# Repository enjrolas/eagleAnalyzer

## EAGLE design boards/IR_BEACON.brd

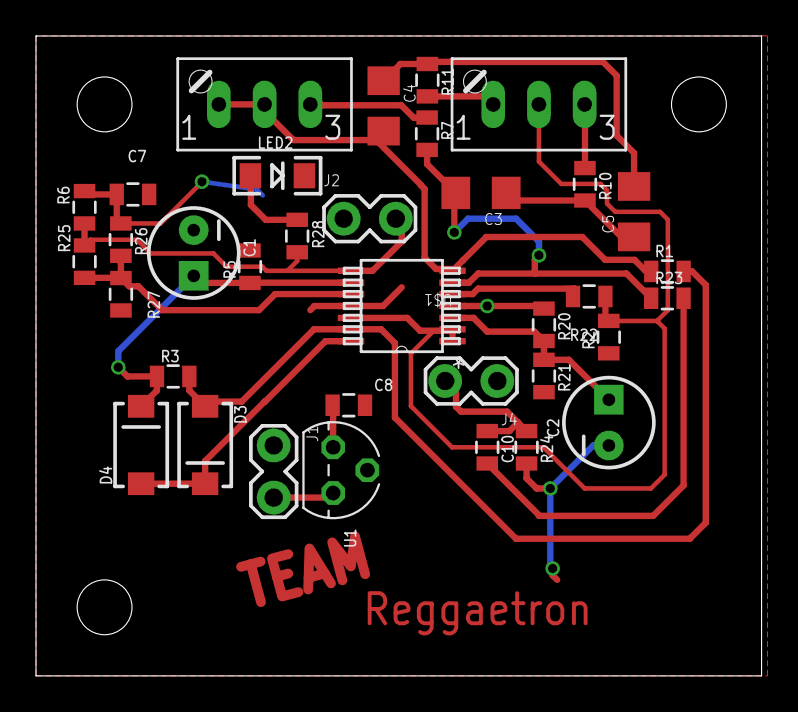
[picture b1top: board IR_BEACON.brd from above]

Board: 2 copper layers, 40.3 x 35.5 mm, 38 parts (0 on the bottom side), 21 nets.

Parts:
1K, 10K: S64W
C1, C2: CPOL-RADIAL-10UF-25V
C3, C4, C5: 47nF; 1206
C7: .1uF; 0805
C8: 2.2uF; 0805
C10: 100nF; 0805
D3, D4: DIODE-SCHOTTKY_; SMA-DIODE
J1, J2, J4: 1X02_LOCK
JP1, JP3, JP5: STAND-OFFTIGHT; STAND-OFF-TIGHT
LED2: LED-1206
R1, R2, R3, R5, R7, R20, R21: 10k; 0805
R6: 3.9k; 0805
R10: 100; 0805
R11, R24: 2.2k; 0805
R22: 20k; 0805
R23: 4.7k; 0805
R25: 1M; 0805
R26: 100k; 0805
R27: 144k; 0805
R28: 330; 0805
U1: LP2950-3.0ACZ; TO92
U$1: MCP6024-X/ST; TSSOP14_MC

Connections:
GND: C1.2, C2.2, C7.2, C8.2, J1.1, J2.1, LED2.C, R5.2, R21.2, R24.2, R27.2, U1.2, U$1.11
unnamed: D3.A, R1.2, R3.2, U$1.13
unnamed: C3.2, R7.2, R23.1, U$1.6
unnamed: 1K.A, R11.2
unnamed: 10K.E, R7.1
unnamed: C3.1, C5.1, R10.2
unnamed: C4.1, C5.2, R11.1
unnamed: 1K.E, R10.1
unnamed: D3.C, D4.A, U$1.14
unnamed: C2.1, R20.2, R21.1, U$1.3
unnamed: R22.2, U$1.5
unnamed: C10.2, R23.2
unnamed: LED2.A, R28.2
VCC: C7.1, C8.1, J4.1, R6.1, R20.1, R26.1, U1.1, U$1.4
VINC+: R25.1, R26.2, R27.1, U$1.10
VOUTC: J2.2, R6.2, R25.2, R28.1, U$1.8
V_BIAS: 1K.S, R2.2, R22.1, U$1.1, U$1.2, U$1.12
V_ENV1: C1.1, D4.C, R3.1, R5.1, U$1.9
V_FILT: 10K.A, 10K.S, C4.2, R1.1, U$1.7
V_IN: J1.2, U1.3
V_IR: C10.1, J4.2, R24.1

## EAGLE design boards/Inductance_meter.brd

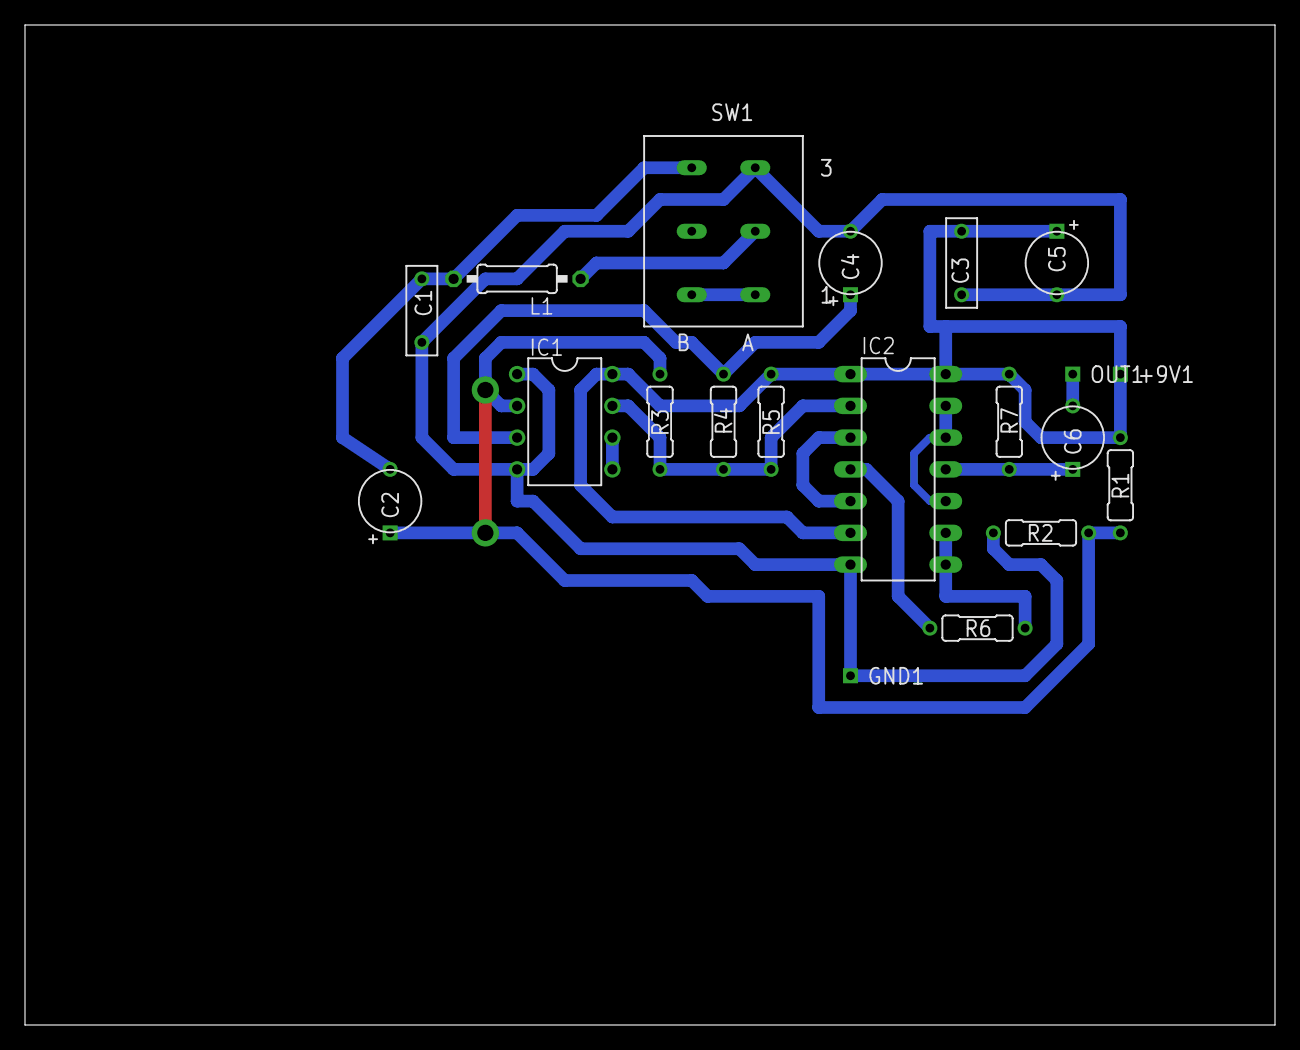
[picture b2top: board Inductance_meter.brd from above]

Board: 2 copper layers, 100.0 x 80.0 mm, 20 parts (0 on the bottom side), 15 nets.

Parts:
+9V1: +9V(T); SQUARE
C1: 970pF; 072X025
C2, C4: 10uF; 050_020_2
C3: 0,1uF; 072X025
C5, C6: 100uF; 050_020_2
GND1: GND(T); SQUARE
IC1: LM311N; DIL08
IC2: 4011N; DIL14
L1: 68uH; 0207/10
OUT1: OUT(T); SQUARE
R1, R2, R3: 100K; R0207/3
R4: 47K; R0207/3
R5, R7: 1K; R0207/3
R6: 150R; R0207/3
SW1: DPDT

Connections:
+9V: +9V1.1, C3.2, C5.+, IC1.8, IC2.1, IC2.6, IC2.14, R1.2, R5.2, R7.1
GND: C1.2, C3.1, C4.-, C5.-, GND1.1, IC1.1, IC1.4, IC2.7, R2.1, SW1.A3
unnamed: L1.1, SW1.A2
unnamed: C1.1, C2.-, L1.2, SW1.B3
unnamed: SW1.A1, SW1.B1
unnamed: IC1.7, IC2.2, R3.1, R4.2, R5.1
unnamed: C2.+, IC1.2, R1.1, R2.2, R3.2
unnamed: IC2.4, R6.2
unnamed: IC1.5, IC1.6
unnamed: C4.+, IC1.3, R4.1
unnamed: IC2.3, IC2.5
unnamed: IC2.8, IC2.9, R6.1
unnamed: IC2.10, IC2.12, IC2.13
unnamed: C6.+, IC2.11, R7.2
OUT: C6.-, OUT1.1

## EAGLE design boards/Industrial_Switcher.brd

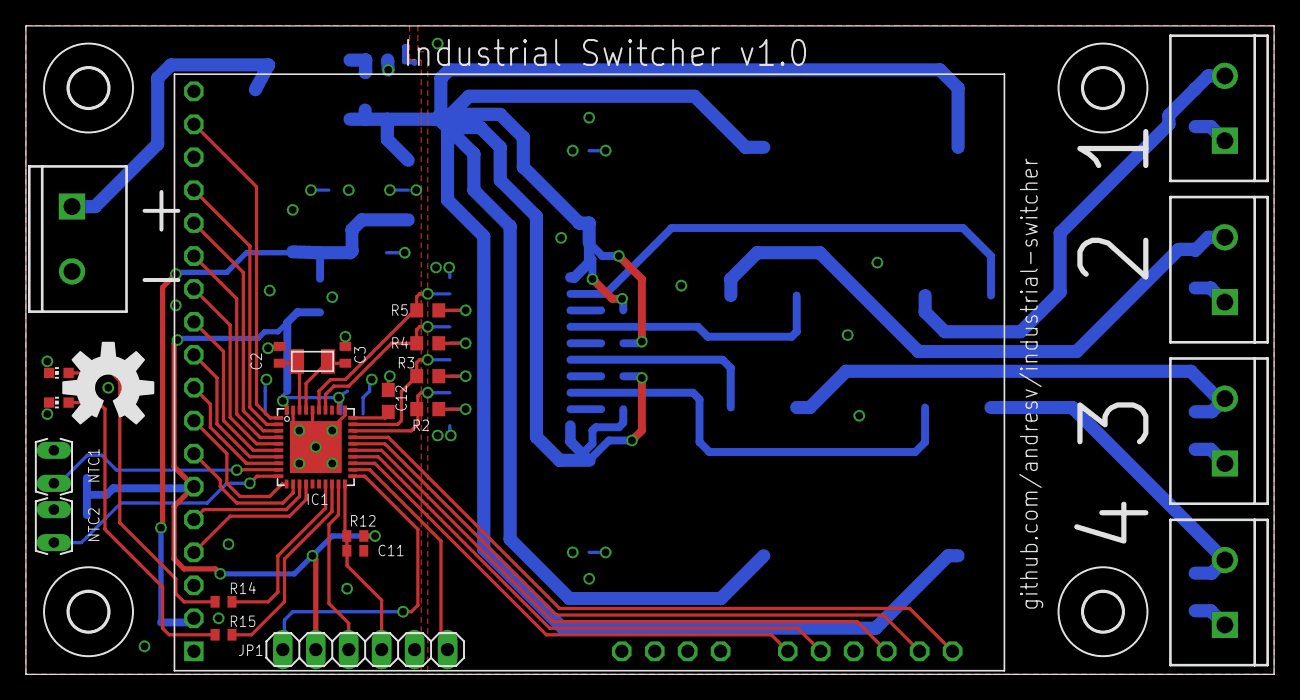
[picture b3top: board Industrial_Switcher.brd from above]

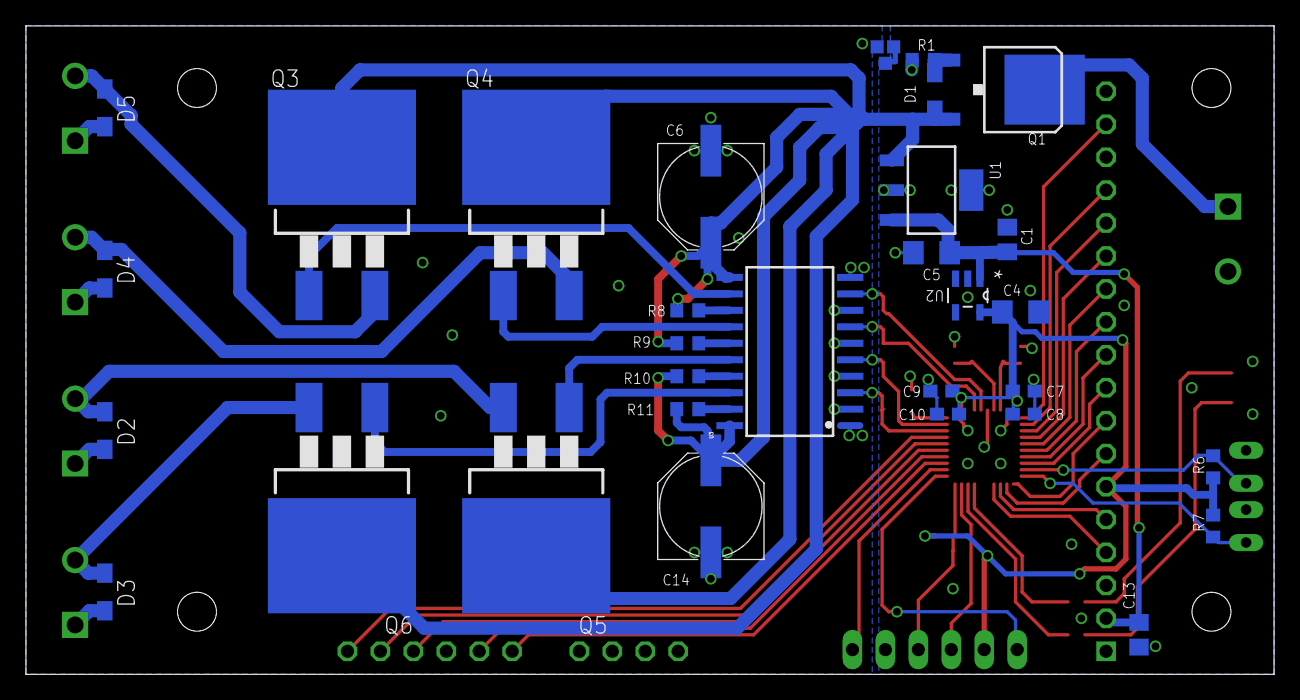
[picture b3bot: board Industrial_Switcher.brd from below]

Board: 2 copper layers, 96.2 x 50.0 mm, 60 parts (31 on the bottom side), 57 nets.

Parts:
C1: 4.7uF; C0805
C2, C3: 9 pF; C0402
C4: 4.7uF; C1206
C5: 10 uF; C1206
C6, C14: 68uF; PANASONIC_F
C7, C9: 10uF; C0603
C8, C10: 100nF; C0603
C11: 2.2nF; C0402
C12: 470nF; C0603
C13: 1uF; C0805
D1: 10V; SOD323-W
D2, D3, D4, D5: 1N4148WS; SOD323-W
H1, H2, H3, H4: 3,0
IC1: MSP430FR5739; RHA40
IC2: HY-TFT220; 2.2TFT
JP1: 1X06
LED1, LED2: CHIP-LED0603
LOAD1, LOAD2, LOAD3, LOAD4: SCREWTERMINAL-5MM-2
LOGO2: OSHW-LOGOL; OSHW-LOGO-L
NTC1, NTC2: 4k7; N640
POWER: SCREWTERMINAL-5MM-2
Q1: IRFR5305; D-PAK_TO252AA
Q2: 32 kHz; ABS07
Q3, Q4, Q5, Q6: IRFZ34NS; D2PACK
R1: 100k; R0603
R2, R3, R4, R5: 2k; R0603
R6, R7: 1k; R0603
R8, R9, R10, R11: 0.01; R0603
R12: 47k; R0402
R14, R15: 1k; R0402
U1: TDA3664; DRFRIEDPARTS/DOAAZ
U2: TPS76933; SOT95P280X145-5N
U3: LT1161CSWPBF; ANDRESV/B3JU7
U$1: GND_CONNECT

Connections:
+3V3: C4.1, C7.2, C8.2, C9.1, C10.1, IC1.32, IC1.40, IC2.RD, JP1.2, R6.2, R7.2, R12.2, U2.5
+5V: C1.1, C5.1, C13.2, IC2.5V, U1.3, U2.1
+24V: C6.+, C14.+, D1.C, Q1.3, Q3.2, Q4.2, Q5.2, Q6.2, R8.2, R9.2, R10.2, R11.2, U1.1, U3.11, U3.20
CS: IC1.2, IC2.CS
DB0: IC1.12, IC2.DB0
DB1: IC1.11, IC2.DB1
DB2: IC1.8, IC2.DB2
DB3: IC1.7, IC2.DB3
DB4: IC1.6, IC2.DB4
DB5: IC1.5, IC2.DB5
DB6: IC1.4, IC2.DB6
DB7: IC1.3, IC2.DB7
DCLK: IC1.27, IC2.DCLK
DCS: IC1.26, IC2.CS1
DIN: IC1.25, IC2.DIN
DIRQ: IC1.23, IC2.PIRQ
DOUT: IC1.24, IC2.DOUT
GND: C1.2, C2.2, C3.2, C4.2, C5.2, C7.1, C8.1, C9.2, C10.2, C11.2, C12.2, C13.1, IC1.31, IC1.36, IC1.39, IC1.TP, IC2.GND, JP1.5, LED1.C, LED2.C, NTC1.1, NTC2.1, POWER.2, R1.1, U1.2, U1.4, U2.2, U2.3, U$1.1, U$1.3
GNDA: C6.-, C14.-, D2.A, D3.A, D4.A, D5.A, LOAD1.1, LOAD2.1, LOAD3.1, LOAD4.1, U3.1, U3.10, U$1.2
LCDRESET: IC1.1, IC2.RESET
LED1: IC1.17, R14.2
LED2: IC1.18, R15.2
unnamed: D1.A, Q1.1, R1.2
unnamed: R5.2, U3.8
unnamed: R8.1, U3.13
unnamed: R9.1, U3.15
unnamed: D3.C, LOAD4.2, Q6.3
unnamed: R10.1, U3.17
unnamed: R4.2, U3.6
unnamed: D2.C, LOAD3.2, Q5.3
unnamed: R11.1, U3.19
unnamed: R3.2, U3.4
unnamed: D4.C, LOAD2.2, Q4.3
unnamed: POWER.1, Q1.4
unnamed: R2.2, U3.2
unnamed: D5.C, LOAD1.2, Q3.3
unnamed: Q6.1, U3.18
unnamed: C3.1, IC1.37, Q2.1
unnamed: C2.1, IC1.38, Q2.2
unnamed: C12.1, IC1.30
unnamed: Q5.1, U3.16
unnamed: Q4.1, U3.14
unnamed: Q3.1, U3.12
unnamed: LED1.A, R14.1
unnamed: LED2.A, R15.1
NTC1: IC1.9, NTC1.2, R6.1
NTC2: IC1.10, NTC2.2, R7.1
OUT1: IC1.28, R2.1, U3.3
OUT2: IC1.29, R3.1, U3.5
OUT3: IC1.34, R4.1, U3.7
OUT4: IC1.35, R5.1, U3.9
RS: IC1.14, IC2.RS
RX: IC1.22, JP1.6
SBWTCK: IC1.19, JP1.3
SBWTDIO: C11.1, IC1.20, JP1.4, R12.1
TX: IC1.21, JP1.1
WR: IC1.13, IC2.WR

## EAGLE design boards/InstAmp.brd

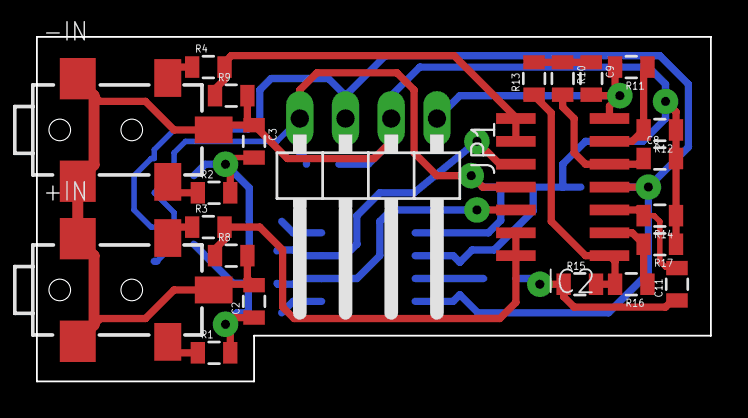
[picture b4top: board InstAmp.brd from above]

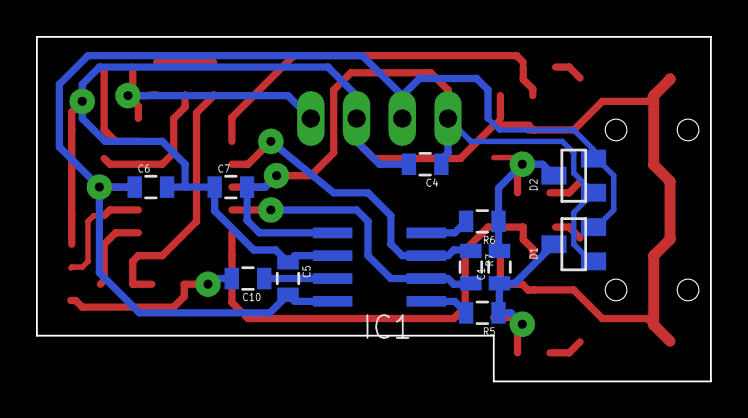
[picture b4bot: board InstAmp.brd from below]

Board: 2 copper layers, 37.4 x 19.1 mm, 35 parts (12 on the bottom side), 24 nets.

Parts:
+IN: AUDIOJACK2.5-SMD
-IN: AUDIOJACK2.5-SMD
C1: 10pF; 0805
C2, C3: 100pF; 0805
C4, C5, C6, C7: 100nF; 0805
C8: 47nF; 0805
C9: 33nF; 0805
C10, C11: 1uF; 0805
D1, D2: BAV199; SOT23
IC1: AD8221ARZ
IC2: TLC2254ID; SO14
JP1: OUT; 1X04/90
R1, R2, R5, R6: 2k2; 0805
R3, R4: 100; 0805
R7: 2k; 0805
R8, R9, R10, R11, R12, R13, R14, R17: 100k; 0805
R15: 680k; 0805
R16: 910k; 0805

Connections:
+5V: C5.2, C6.1, D1.2, D2.2, IC1.8, IC2.4, JP1.3
-5V: C4.1, C7.2, D1.1, D2.1, IC1.5, IC2.11, JP1.4
GND: +IN.GND1, +IN.GND2, +IN.SW, -IN.GND1, -IN.GND2, -IN.SW, C2.2, C3.1, C4.2, C5.1, C6.2, C7.1, C8.2, IC1.6, JP1.2, R8.2, R9.2, R12.1, R14.1, R17.1
unnamed: +IN.L, R1.1
unnamed: -IN.R, R4.1
unnamed: +IN.R, R3.1
unnamed: -IN.L, R2.1
unnamed: C1.2, C3.2, D2.3, R2.2, R6.1
unnamed: C1.1, C2.1, D1.3, R1.2, R5.1
unnamed: IC2.8, IC2.9, R4.2, R9.1
unnamed: IC1.3, IC2.10, R7.1
unnamed: IC2.1, R13.1, R15.2, R16.2
unnamed: IC2.2, R16.1, R17.2
unnamed: C10.1, IC1.7
unnamed: IC1.1, R5.2
unnamed: IC1.4, R6.2
unnamed: C8.1, IC2.5, R10.2
unnamed: C9.1, R10.1, R13.2
unnamed: IC1.2, IC2.12, R7.2
unnamed: IC2.13, IC2.14, R3.2, R8.1
unnamed: C10.2, C11.1, R15.1
unnamed: C11.2, IC2.3, R14.2
unnamed: IC2.6, R11.1, R12.2
OUT: C9.2, IC2.7, JP1.1, R11.2

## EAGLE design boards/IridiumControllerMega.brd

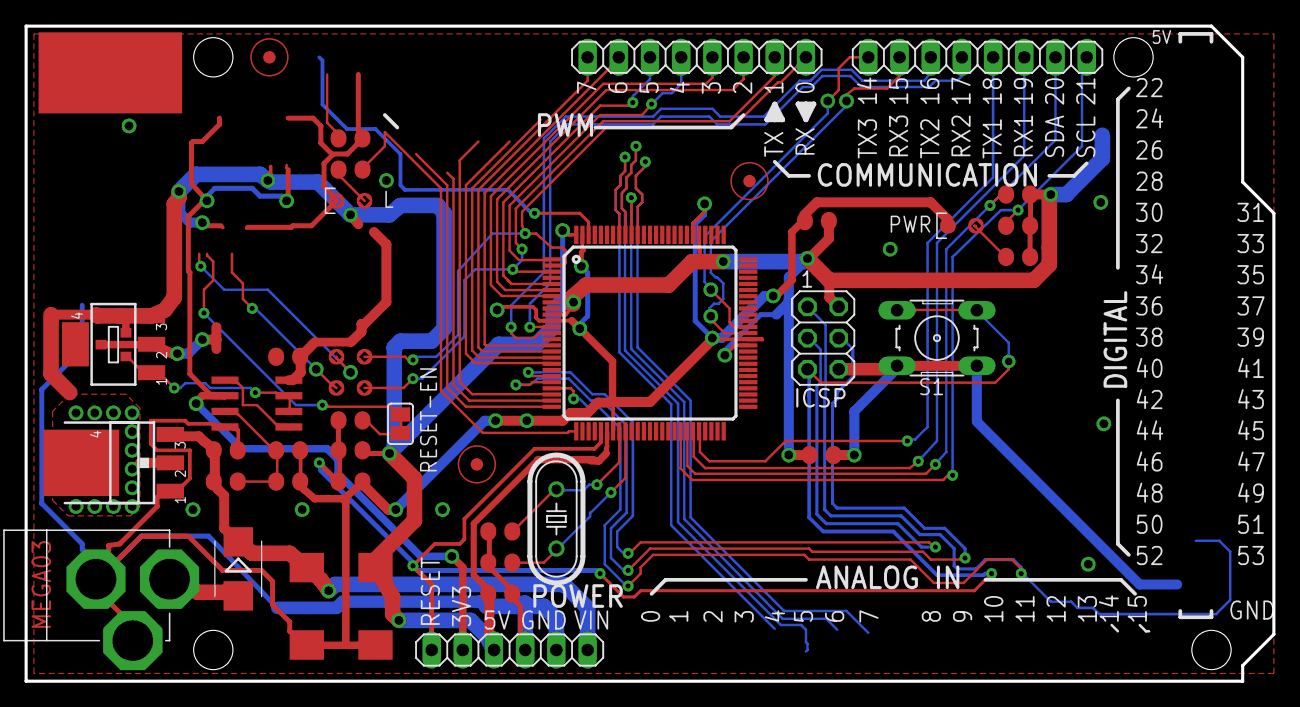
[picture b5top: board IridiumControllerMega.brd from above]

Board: 2 copper layers, 101.6 x 53.3 mm, 42 parts (0 on the bottom side), 35 nets.

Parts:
C1, C4, C5, C9, C10, C12, C13, C17: 100n; C0805RND
C2, C3, C11: 22p; C0805RND
C6, C7: 100u; SMC_D
COMMUNICATION: 1X08
D1: SMB
IC2: ATMEGA1280-16AU; TQFP100
IC4: MC33269D-5.0; DPACK
IC5: MC33269ST-5.0T3; SOT223
IC7: LM358D; SO08
ICSP: ICSP; 2X03
L: 0805RND
POWER: 1X06
PWML: 1X08
PWR: 0805RND
Q2: 16MHz; HC49/S
R1, R8: 1K; R0805RND
R2, R3, R6, R10: 10k; R0805RND
R5: 10K; R0805RND
R11, R12: 1K; RCL_0805RND
RESET-EN: SJ
S1: B3F-10XX
T1: NDT2955; SOT223
T2: FDN340P; SOT-23
U$1, U$2, U$3: FIDUCIALMOUNT; FIDUCIA-MOUNT
X2: DC21MMX; DC-21MM

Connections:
+3V3: IC7.2, POWER.2
+5V: C1.1, C7.+, C9.1, C10.1, C17.2, IC2.10, IC2.31, IC2.61, IC2.80, IC2.100, IC4.2, IC5.2, IC5.4, IC7.8, ICSP.2, POWER.3, R2.1, R3.1, R5.2, R8.1, T1.3, T2.2
AREF: C4.1, IC2.98
CMP: C13.2, IC7.3, R6.2, R10.1
DTR: C12.1, RESET-EN.1, RESET-EN.2
GATE_CMD: IC7.6, IC7.7, T1.1, T2.3
GND: C1.2, C2.1, C3.1, C4.2, C5.2, C6.-, C7.-, C9.2, C10.2, C11.2, C13.1, C17.1, IC2.11, IC2.32, IC2.62, IC2.81, IC2.99, IC4.1, IC5.1, IC7.4, ICSP.6, L.P$2, POWER.4, POWER.5, PWR.P$2, R6.1, S1.1, S1.2, X2.1, X2.3
unnamed: L.P$1, R1.2
unnamed: PWR.P$1, R8.2
unnamed: IC7.1, IC7.5
unnamed: C2.2, IC2.34, Q2.1
unnamed: C3.2, IC2.33, Q2.2
PB1: IC2.20, ICSP.3
PB2: IC2.21, ICSP.4
PB3: IC2.22, ICSP.1
PB7: IC2.26, R1.1
PE0: IC2.2, PWML.1, R11.P$2
PE1: IC2.3, PWML.2, R12.P$2
PE4: IC2.6, PWML.3
PE5: IC2.7, PWML.4
PG5: IC2.1, PWML.5
PH3: IC2.15, PWML.7
PH4: IC2.16, PWML.8
PWRIN: D1.A, X2.2
RESET: C11.1, C12.2, IC2.30, ICSP.5, POWER.1, R5.1, S1.3, S1.4
RXD1: COMMUNICATION.3, IC2.45
RXD2: COMMUNICATION.5, IC2.12
RXD3: COMMUNICATION.7, IC2.63
SCL: COMMUNICATION.1, IC2.43, R2.2
SDA: COMMUNICATION.2, IC2.44, R3.2
TXD1: COMMUNICATION.4, IC2.46
TXD2: COMMUNICATION.6, IC2.13
TXD3: COMMUNICATION.8, IC2.64
USBVCC: T1.2, T2.1
VIN: C5.1, C6.+, D1.C, IC4.3, IC5.3, POWER.6, R10.2

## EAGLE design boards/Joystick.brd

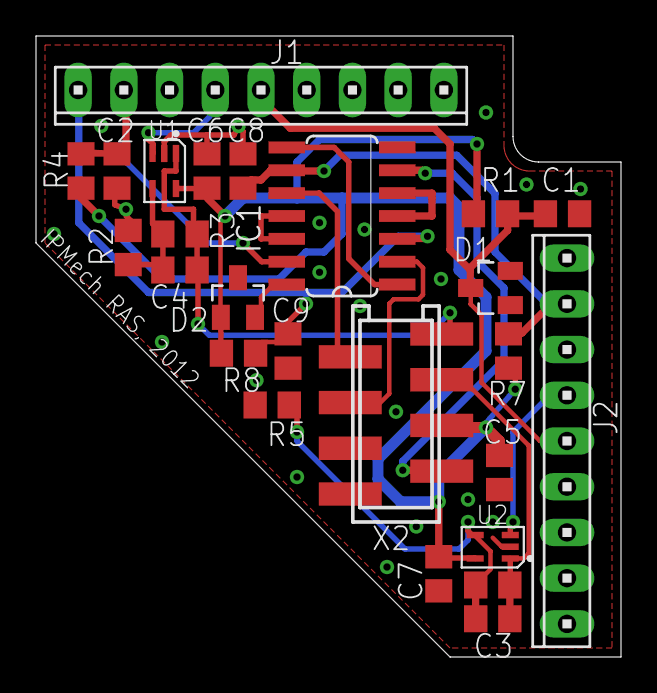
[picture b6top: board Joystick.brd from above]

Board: 2 copper layers, 32.5 x 34.5 mm, 25 parts (0 on the bottom side), 19 nets.

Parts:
C1, C2, C8, C9: 1uF; C0805
C3, C4, C6, C7: 0.1uF; C0805
C5: 10uF; C0805
D1: BZX84-C4V7; SOT23
D2: BAV199; SOT23
IC1: 74HC14D; SO14
J1, J2: 10X09MTA
R1: 100R 5%; R0805
R2, R5: 2K5 1%; R0805
R3, R6: 1K6 1%; R0805
R4, R7, R8: 1K 5%; R0805
U1, U2: AD8627AKS; SC70(KS-5)
X2: 7-188275-8; MMT-F-SMD-8

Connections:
+4V7: C1.1, D1.3, J1.5, J2.5, R1.2
+5V: C5.1, C6.1, C7.1, D2.1, R1.1, R4.2, R7.2, R8.2, U1.5, U2.5, X2.5
GNDA: C1.2, C2.2, C5.2, C6.2, C7.2, C8.2, C9.2, D1.1, IC1.7, J1.3, J1.7, J1.8, J1.9, J2.1, J2.3, J2.7, J2.8, J2.9, R2.1, R5.1, U1.2, U2.2, X2.6
unnamed: J2.4, U2.3
unnamed: C3.1, R5.2, R6.1, U2.4
unnamed: C3.2, R6.2, U2.1, X2.3
unnamed: IC1.4, IC1.5
unnamed: IC1.10, X2.2
unnamed: D2.2, IC1.14
unnamed: IC1.11, IC1.12
unnamed: IC1.1, IC1.8
unnamed: C2.1, IC1.13, J1.2, R4.1
unnamed: IC1.2, X2.4
unnamed: C8.1, IC1.9, J2.2, R7.1
unnamed: C9.1, IC1.3, J1.1, R8.1
unnamed: J1.4, U1.3
unnamed: C4.1, R2.2, R3.1, U1.4
unnamed: C4.2, R3.2, U1.1, X2.1
TOTMANN_TASTE: IC1.6, X2.7

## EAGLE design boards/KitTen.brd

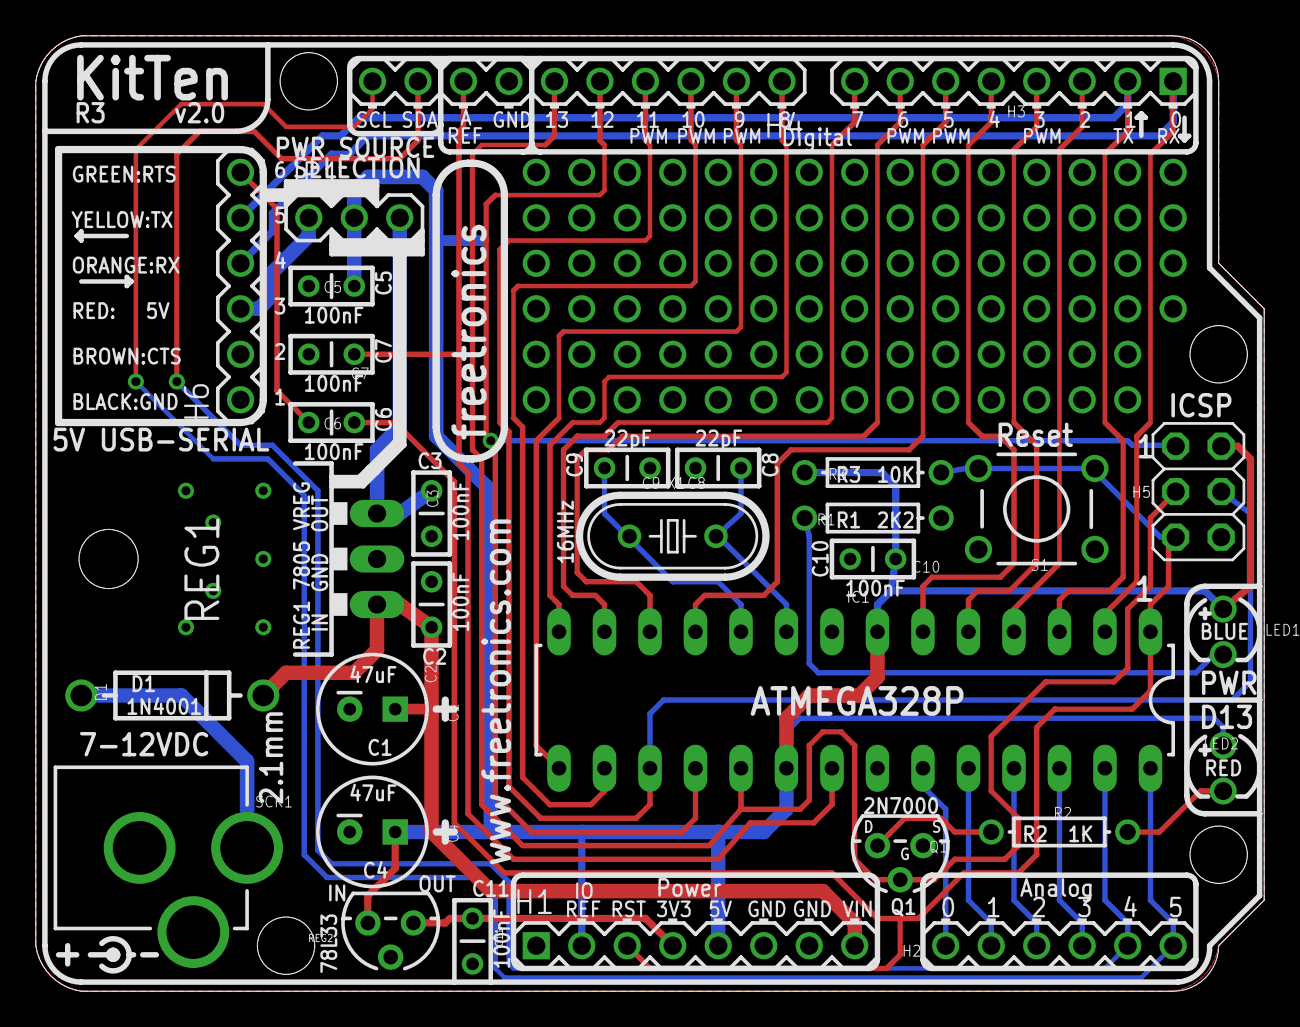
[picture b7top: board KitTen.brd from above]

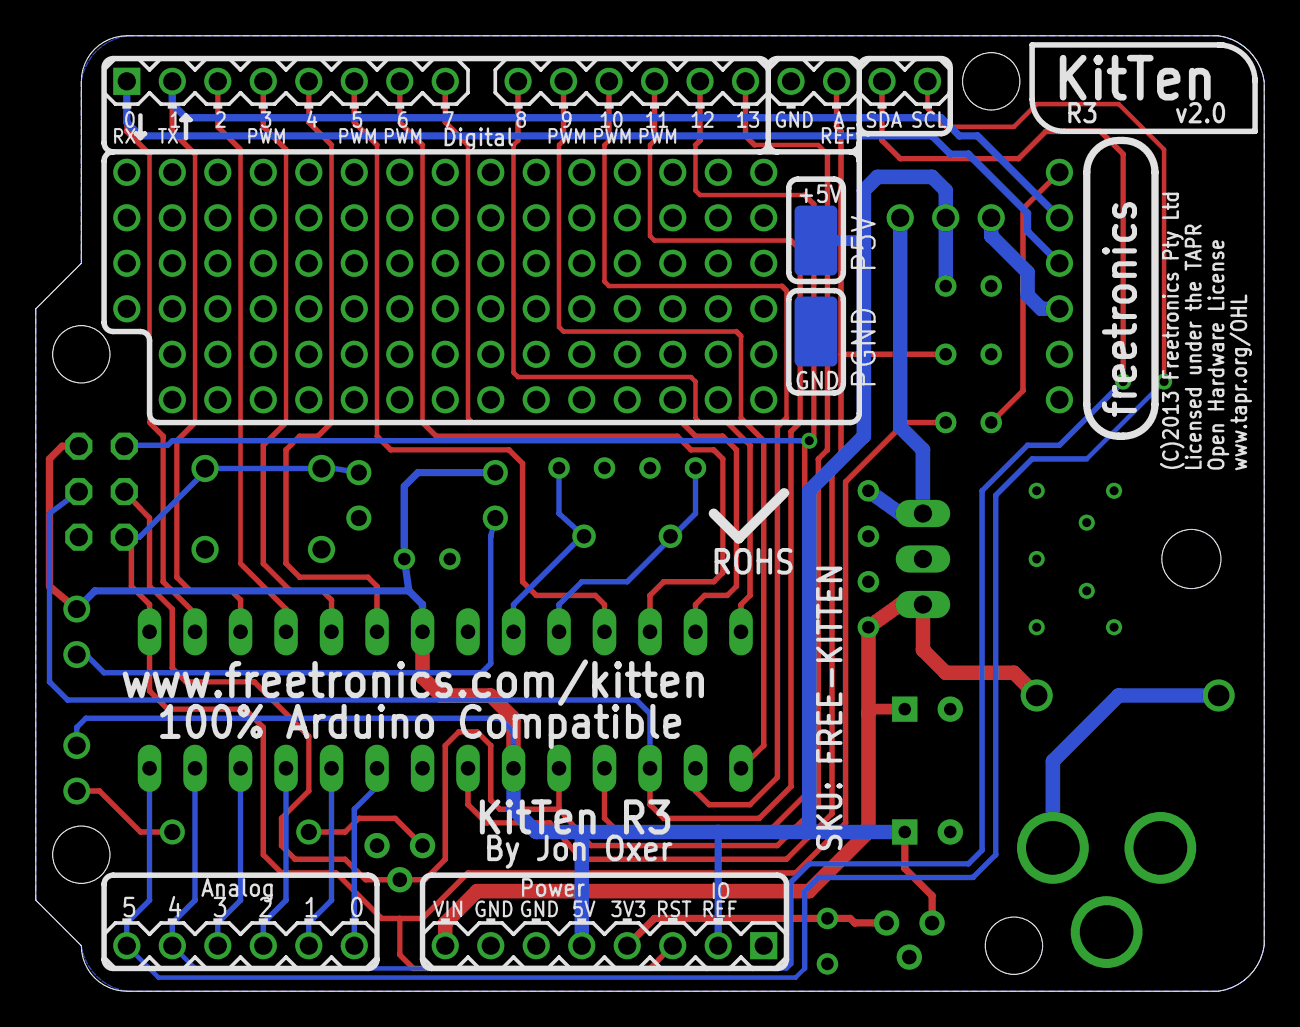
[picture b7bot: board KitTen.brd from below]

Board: 2 copper layers, 68.6 x 53.3 mm, 33 parts (2 on the bottom side), 35 nets.

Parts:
C1, C4: 47uF 25V; CPOL-RADIAL-10UF-25V
C2, C3, C5, C6, C7, C10, C11: 100nF; CAP-PTH-SMALL
C8, C9: 22pF; CAP-PTH-SMALL
D1: 1N4001; DIODE-1N4001
H1, H3: Digital_0_7; 1X08
H2: Analog; 1X06
H4: M100.1; 1X10
H5: ICSP; 2X03
H6: USB-TTL; 1X06
IC1: ATMEGA328P; DIL28-3
JP1: PWR SELECT; 1X03
LED1: PWR/BLUE; LED3MM
LED2: D13; LED3MM
P5V: LUXEON-PAD
PGND: LUXEON-PAD
Q1: 2N7000; TO92
R1: 2K2; AXIAL-0.3
R2: 1K; AXIAL-0.3
R3: 10K; AXIAL-0.3
REG1: 7805; 78XXL
REG2: 78L33; TO92
S1: RESET; TACTILE-PTH
SCK1: DC_2_1MM; POWER_JACK_PTH
X1: 16MHz HC49S; HC49U-V

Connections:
3V3: C11.1, H1.4, REG2.1
5V: C4.1, C5.1, C10.1, H1.2, H1.5, H5.2, IC1.7, IC1.20, JP1.2, LED1.A, LED2.A, P5V.P$1, R3.P$2, REG2.3
A0: H2.1, IC1.23
A1: H2.2, IC1.24
A2: H2.3, IC1.25
A3: H2.4, IC1.26
A4_SDA: H2.5, H4.9, IC1.27
A5_SCL: H2.6, H4.10, IC1.28
AREF: C7.1, H4.8, IC1.21
D0_RX: H3.1, H6.4, IC1.2
D1_TX: H3.2, H6.5, IC1.3
D2: H3.3, IC1.4
D3: H3.4, IC1.5
D4: H3.5, IC1.6
D5: H3.6, IC1.11
D6: H3.7, IC1.12
D7: H3.8, IC1.13
D8: H4.1, IC1.14
D9: H4.2, IC1.15
D10: H4.3, IC1.16
D11_MOSI: H4.4, H5.4, IC1.17
D12_MISO: H4.5, H5.1, IC1.18
D13_SCK: H4.6, H5.3, IC1.19, Q1.2
EXT_5V: C3.1, JP1.3, REG1.OUT
GND: C1.2, C2.2, C3.2, C4.2, C5.2, C7.2, C8.1, C9.1, C10.2, C11.2, H1.6, H1.7, H4.7, H5.6, H6.1, H6.2, IC1.8, IC1.22, PGND.P$1, Q1.1, R1.P$1, REG1.GND, REG2.2, S1.1, S1.2, SCK1.GND, SCK1.GNDBREAK
unnamed: LED2.K, R2.P$2
unnamed: C8.2, IC1.9, X1.2
unnamed: Q1.3, R2.P$1
unnamed: C9.2, IC1.10, X1.1
unnamed: D1.A, SCK1.PWR
unnamed: LED1.K, R1.P$2
RESET: C6.2, H1.3, H5.5, IC1.1, R3.P$1, S1.3, S1.4
RTS: C6.1, H6.6
USB_5V: H6.3, JP1.1
VIN: C1.1, C2.1, D1.C, H1.8, REG1.IN

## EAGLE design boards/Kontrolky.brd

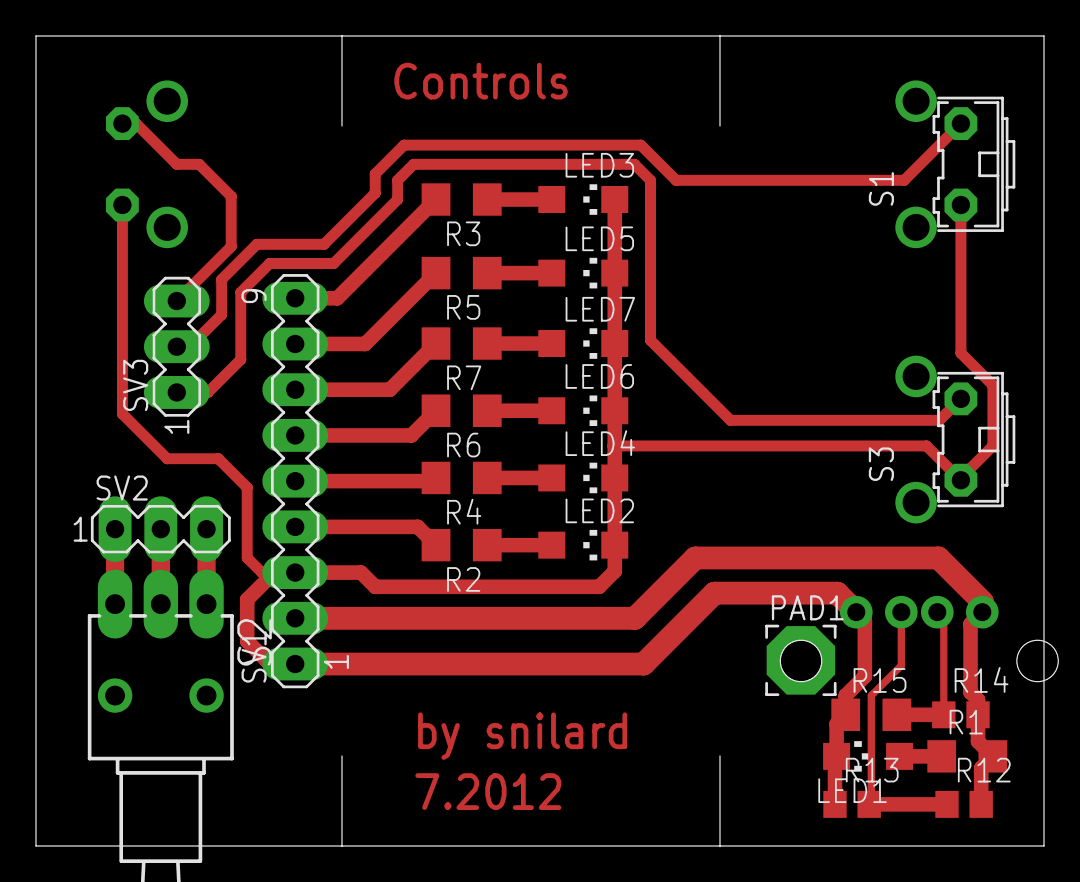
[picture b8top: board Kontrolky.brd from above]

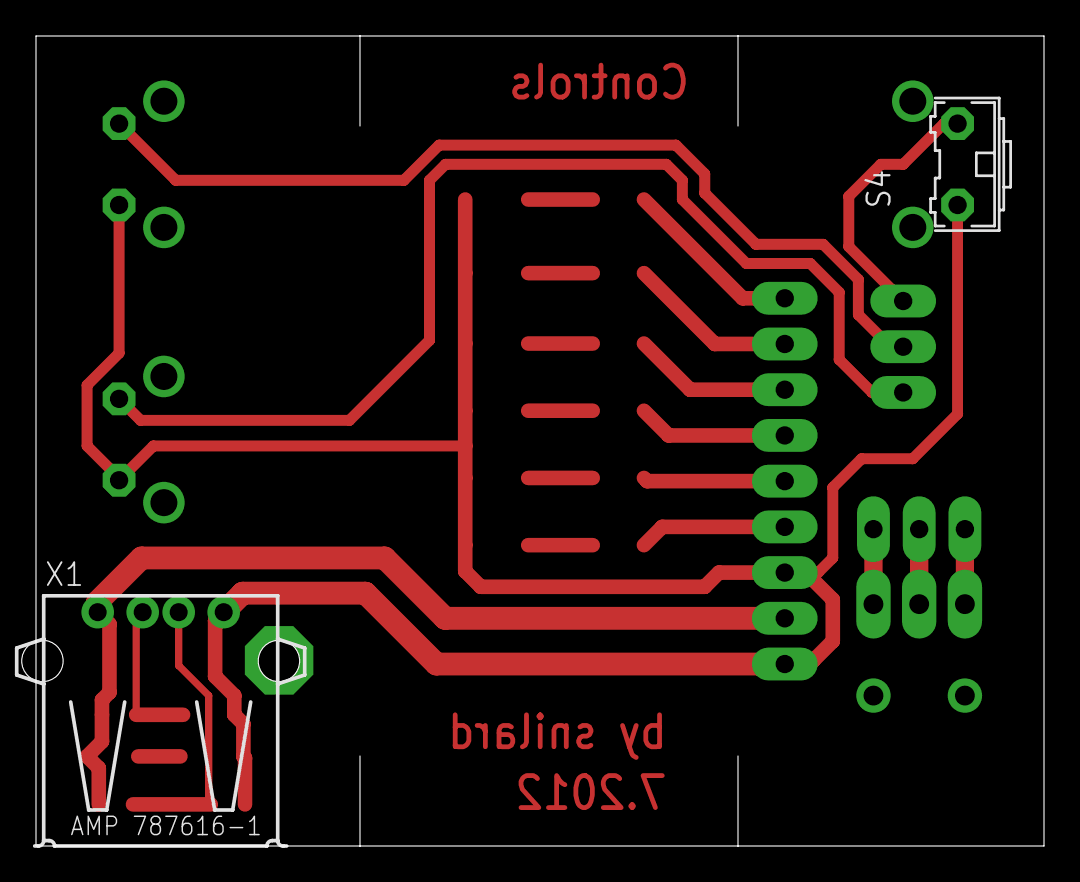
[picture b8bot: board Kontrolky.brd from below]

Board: 2 copper layers, 56.0 x 45.0 mm, 27 parts (2 on the bottom side), 23 nets.

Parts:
LED1, LED2, LED3, LED4, LED5, LED6, LED7: CHIPLED_1206
PAD1: 3,81/1,4
R1, R2, R3, R4, R5, R6, R7: 33K; R1206
R12, R14: 33K; R0805
R13: 23K; R0805
R15: 47K; R1206
S1, S3, S4: DTS-6; B3F-31XX
S2: TL36WO; TL3XWO
SV1: MA09-1
SV2, SV3: MA03-1
X1: USB

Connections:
GND: LED1.C, LED2.C, LED3.C, LED4.C, LED5.C, LED6.C, LED7.C, R13.1, R15.1, S1.1, S3.1, S4.1, SV1.1, SV1.3, X1.4
unnamed: LED1.A, R1.1
unnamed: LED2.A, R2.1
unnamed: LED3.A, R3.1
unnamed: LED4.A, R4.1
unnamed: LED5.A, R5.1
unnamed: LED7.A, R7.1
unnamed: LED6.A, R6.1
unnamed: R2.2, SV1.4
unnamed: R3.2, SV1.9
unnamed: R4.2, SV1.5
unnamed: R5.2, SV1.8
unnamed: R6.2, SV1.6
unnamed: R7.2, SV1.7
unnamed: S2.2, SV2.2
unnamed: S2.1, SV2.3
unnamed: S2.3, SV2.1
unnamed: S1.2, SV3.2
unnamed: S4.2, SV3.3
unnamed: S3.2, SV3.1
unnamed: R12.1, R13.2, X1.3
unnamed: R14.1, R15.2, X1.2
unnamed: R1.2, R12.2, R14.2, SV1.2, X1.1

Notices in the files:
boards/KitTen.brd:
Licensed under the TAPR
Open Hardware License
(C)2013 Freetronics Pty Ltd
parts and their libraries:
SparkFun-Passives: Licensing: CC v3.0 Share-Alike You are welcome to use this library for commercial purposes.
